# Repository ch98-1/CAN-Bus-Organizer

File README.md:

# CAN-Bus-Organizer

Organizer for a CAN bus. Secure board with M4 screw.

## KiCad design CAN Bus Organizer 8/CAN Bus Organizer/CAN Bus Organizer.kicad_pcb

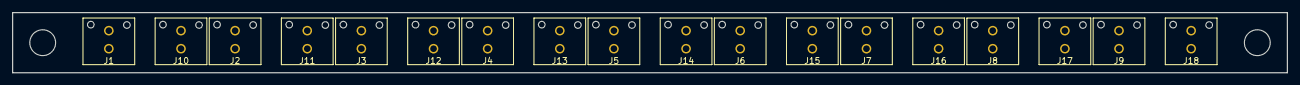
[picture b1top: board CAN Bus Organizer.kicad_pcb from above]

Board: 2 copper layers, 212.0 x 10.0 mm, 20 parts (0 on the bottom side), 18 nets, no tracks yet.

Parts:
J1, J2, J3, J4, J5, J6, J7, J8, J9, J10, J11, J12, J13, J14, J15, J16, J17, J18: Conn_01x02_Male; Molex_Microfit3_Header_02x01_Straight_43045-0228
MK1, MK2: Mounting_Hole; MountingHole_4.3mm_M4

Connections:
unnamed: J1.1, J10.1
unnamed: J1.2, J10.2
unnamed: J2.1, J11.1
unnamed: J2.2, J11.2
unnamed: J3.1, J12.1
unnamed: J3.2, J12.2
unnamed: J4.1, J13.1
unnamed: J4.2, J13.2
unnamed: J5.1, J14.1
unnamed: J5.2, J14.2
unnamed: J6.1, J15.1
unnamed: J6.2, J15.2
unnamed: J7.1, J16.1
unnamed: J7.2, J16.2
unnamed: J8.1, J17.1
unnamed: J8.2, J17.2
unnamed: J9.1, J18.1
unnamed: J9.2, J18.2

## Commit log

2018-03-18 Finished the board
2018-03-18 Finished board layout
2018-03-19 Changed board name
